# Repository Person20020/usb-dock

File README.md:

# USB Dock

This is a USB hub with a USB C input and 3 USB C outputs. It also includes a PCM2902 DAC/ADC to plug in headphones.

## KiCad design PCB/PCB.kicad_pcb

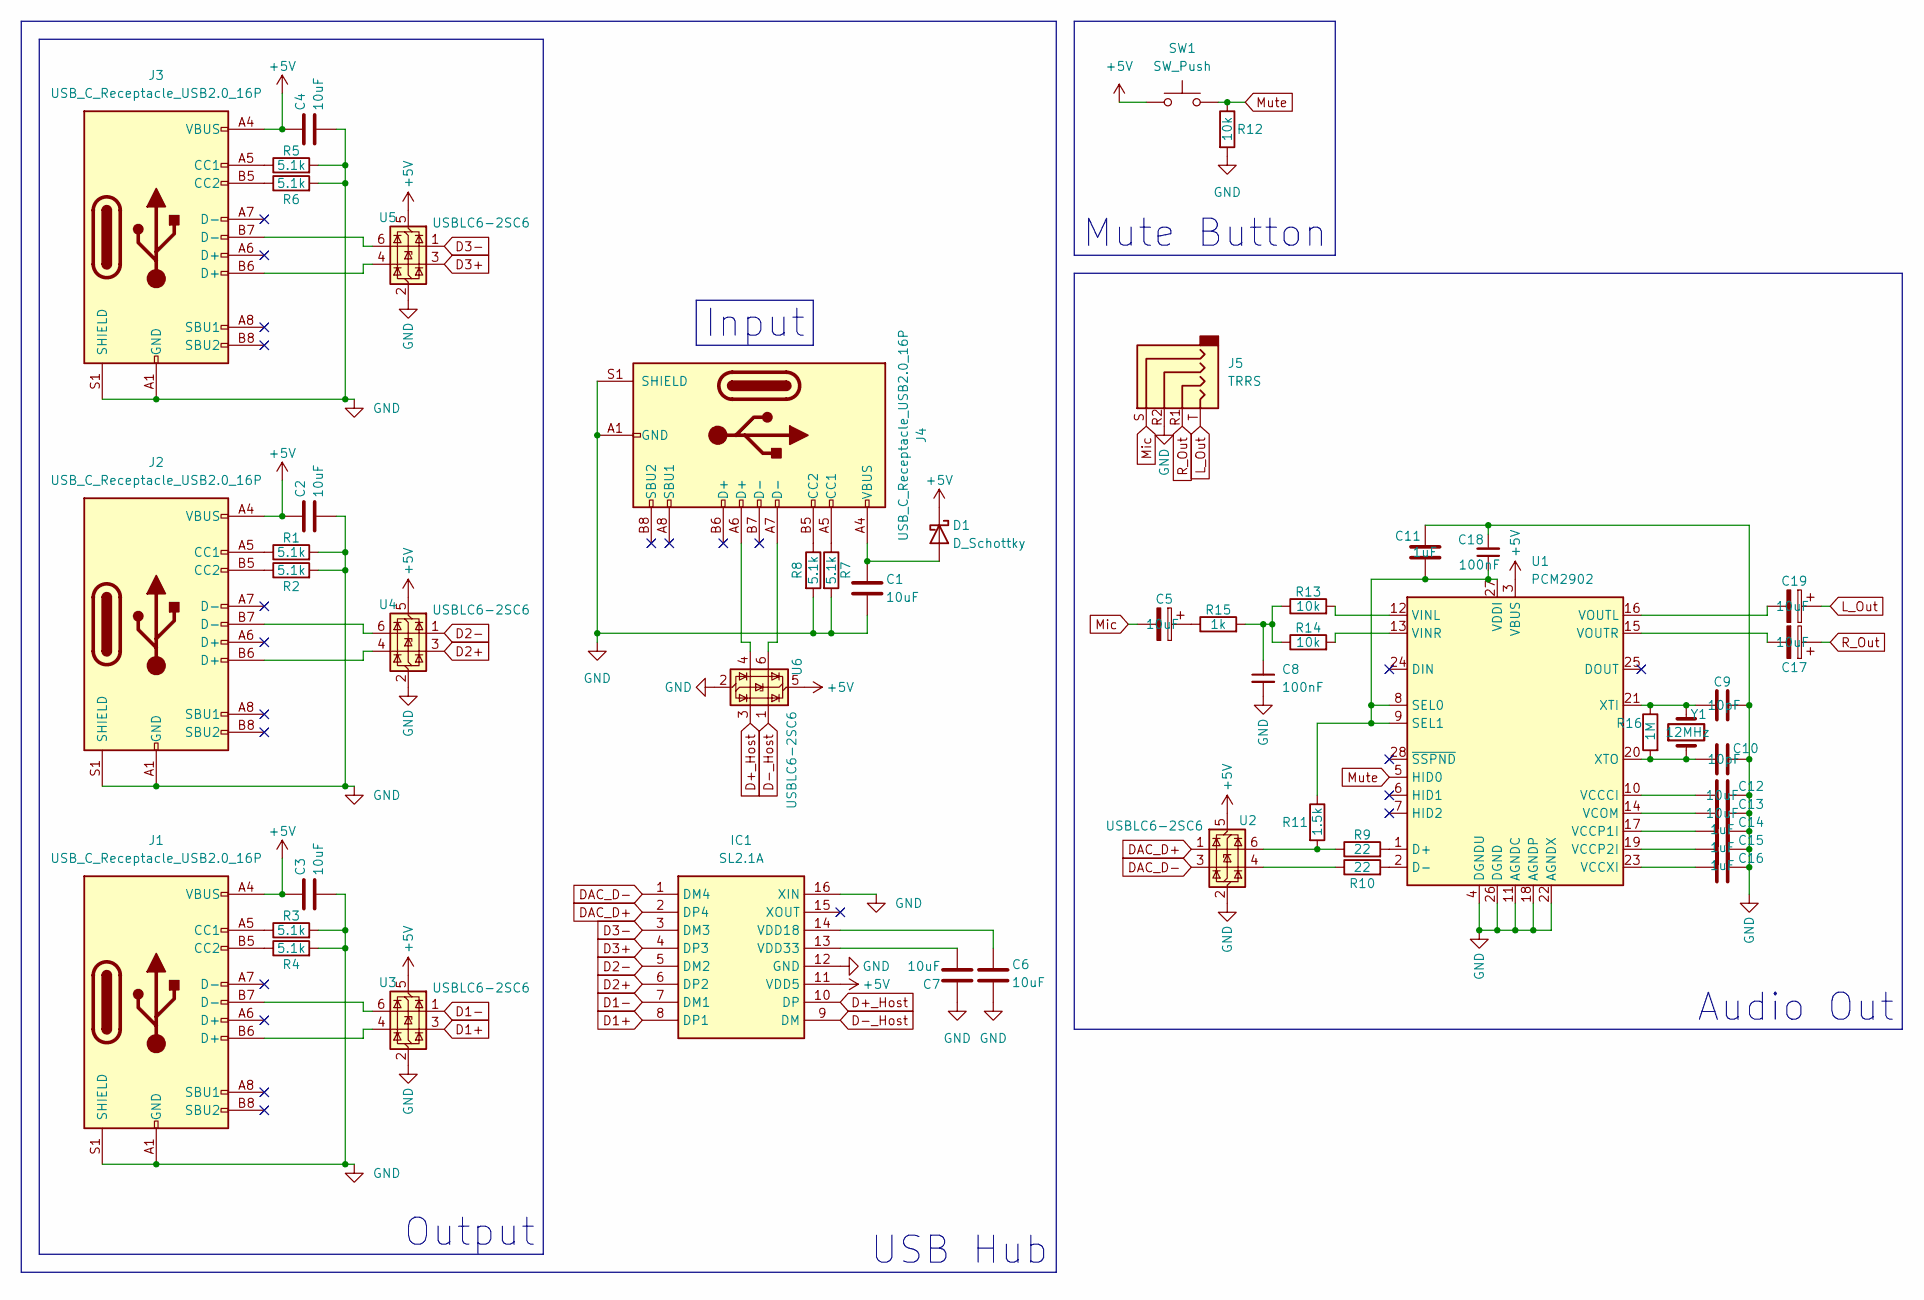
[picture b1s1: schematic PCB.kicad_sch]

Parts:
C1, C2, C3, C4, C5, C6, C7, C12, C13, C17, C19: 10uF; C_1206_3216Metric_Pad1.33x1.80mm_HandSolder
C8, C18: 100nF; C_1206_3216Metric_Pad1.33x1.80mm_HandSolder
C9, C10: 10pF; C_1206_3216Metric_Pad1.33x1.80mm_HandSolder
C11, C14, C15, C16: 1uF; C_1206_3216Metric_Pad1.33x1.80mm_HandSolder
D1: D_Schottky; D_1206_3216Metric_Pad1.42x1.75mm_HandSolder
IC1: SL2.1A; SOP-16_3.9x9.9mm_P1.27mm; Manufacturer_Part_Number SL2.1A
J1, J2, J3, J4: USB_C_Receptacle_USB2.0_16P; USB_C_Receptacle_GCT_USB4110
J5: TRRS; Jack_3.5mm_PJ320D_Horizontal
R1, R2, R3, R4, R5, R6, R7, R8: 5.1k; R_1206_3216Metric_Pad1.30x1.75mm_HandSolder
R9, R10: 22; R_1206_3216Metric_Pad1.30x1.75mm_HandSolder
R11: 1.5k; R_1206_3216Metric_Pad1.30x1.75mm_HandSolder
R12, R13, R14: 10k; R_1206_3216Metric_Pad1.30x1.75mm_HandSolder
R15: 1k; R_1206_3216Metric_Pad1.30x1.75mm_HandSolder
R16: 1M; R_1206_3216Metric_Pad1.30x1.75mm_HandSolder
SW1: SW_Push; SW_PUSH-12mm_Wuerth-430476085716
U1: PCM2902; SSOP-28_5.3x10.2mm_P0.65mm
U2, U3, U4, U5, U6: USBLC6-2SC6; SOT-23-6
Y1: 12MHz; Crystal_HC49-4H_Vertical

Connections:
+5V: C2.2, C3.2, C4.2, D1.1 (K), IC1.11 (VDD5), J1.A4 (VBUS), J1.A9 (VBUS), J1.B4 (VBUS), J1.B9 (VBUS), J2.A4 (VBUS), J2.A9 (VBUS), J2.B4 (VBUS), J2.B9 (VBUS), J3.A4 (VBUS), J3.A9 (VBUS), J3.B4 (VBUS), J3.B9 (VBUS), SW1.1, U1.3 (VBUS), U2.5 (VBUS), U3.5 (VBUS), U4.5 (VBUS), U5.5 (VBUS), U6.5 (VBUS)
D1+: IC1.8 (DP1), U3.3 (I/O2)
D1-: IC1.7 (DM1), U3.1 (I/O1)
D2+: IC1.6 (DP2), U4.3 (I/O2)
D2-: IC1.5 (DM2), U4.1 (I/O1)
D3+: IC1.4 (DP3), U5.3 (I/O2)
D3-: IC1.3 (DM3), U5.1 (I/O1)
D+_Host: IC1.10 (DP), U6.3 (I/O2)
D-_Host: IC1.9 (DM), U6.1 (I/O1)
DAC_D+: IC1.2 (DP4), U2.1 (I/O1)
DAC_D-: IC1.1 (DM4), U2.3 (I/O2)
GND: C1.1, C2.1, C3.1, C4.1, C6.1, C7.1, C8.2, C9.2, C10.2, C11.1, C12.2, C13.2, C14.2, C15.2, C16.2, C18.2, IC1.12 (GND), IC1.16 (XIN), J1.A1 (GND), J1.A12 (GND), J1.B1 (GND), J1.B12 (GND), J1.S1 (SHIELD), J2.A1 (GND), J2.A12 (GND), J2.B1 (GND), J2.B12 (GND), J2.S1 (SHIELD), J3.A1 (GND), J3.A12 (GND), J3.B1 (GND), J3.B12 (GND), J3.S1 (SHIELD), J4.A1 (GND), J4.A12 (GND), J4.B1 (GND), J4.B12 (GND), J4.S1 (SHIELD), J5.R2, R1.2, R2.2, R3.2, R4.2, R5.2, R6.2, R7.2, R8.2, R12.2, U1.4 (DGNDU), U1.11 (AGNDC), U1.18 (AGNDP), U1.22 (AGNDX), U1.26 (DGND), U2.2 (GND), U3.2 (GND), U4.2 (GND), U5.2 (GND), U6.2 (GND)
L_Out: C19.1, J5.T
Mic: C5.2, J5.S
Mute: R12.1, SW1.2, U1.5 (HID0)
unnamed: C5.1, R15.1
unnamed: C8.1, R13.1, R14.1, R15.2
unnamed: C1.2, D1.2 (A), J4.A4 (VBUS), J4.A9 (VBUS), J4.B4 (VBUS), J4.B9 (VBUS)
unnamed: C6.2, IC1.14 (VDD18)
unnamed: C7.2, IC1.13 (VDD33)
unnamed: J1.A5 (CC1), R3.1
unnamed: J1.B5 (CC2), R4.1
unnamed: J1.B6 (D+), U3.4 (I/O2)
unnamed: J1.B7 (D-), U3.6 (I/O1)
unnamed: J2.A5 (CC1), R1.1
unnamed: J2.B5 (CC2), R2.1
unnamed: J2.B6 (D+), U4.4 (I/O2)
unnamed: J2.B7 (D-), U4.6 (I/O1)
unnamed: J3.A5 (CC1), R5.1
unnamed: J3.B5 (CC2), R6.1
unnamed: J3.B6 (D+), U5.4 (I/O2)
unnamed: J3.B7 (D-), U5.6 (I/O1)
unnamed: J4.A5 (CC1), R7.1
unnamed: J4.B5 (CC2), R8.1
unnamed: J4.A6 (D+), U6.4 (I/O2)
unnamed: J4.A7 (D-), U6.6 (I/O1)
unnamed: R10.1, U2.4 (I/O2)
unnamed: R9.1, R11.2, U2.6 (I/O1)
unnamed: R9.2, U1.1 (D+)
unnamed: R10.2, U1.2 (D-)
unnamed: C11.2, C18.1, R11.1, U1.8 (SEL0), U1.9 (SEL1), U1.27 (VDDI)
unnamed: C12.1, U1.10 (VCCCI)
unnamed: C14.1, U1.17 (VCCP1I)
unnamed: C15.1, U1.19 (VCCP2I)
unnamed: C16.1, U1.23 (VCCXI)
unnamed: C13.1, U1.14 (VCOM)
unnamed: R13.2, U1.12 (VINL)
unnamed: R14.2, U1.13 (VINR)
unnamed: C19.2, U1.16 (VOUTL)
unnamed: C17.2, U1.15 (VOUTR)
unnamed: C9.1, R16.1, U1.21 (XTI), Y1.2
unnamed: C10.1, R16.2, U1.20 (XTO), Y1.1
R_Out: C17.1, J5.R1

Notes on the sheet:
Audio Out
USB Hub
Output
Input
Mute Button

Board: 2 copper layers, 50 parts (0 on the bottom side), 53 nets, no tracks yet.

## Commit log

2025-07-31 finished schematic
2025-07-31 fixed usb data lines + cleaned up schematic
